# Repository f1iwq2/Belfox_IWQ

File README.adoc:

Carte BELFOX IWQ
================
Carte de remplacement pour portail coulissants BELFOX
pour pilotage de moteurs à courant continu - A base d'arduino nano

Documents dans le fichier pdf
Fichiers schéma Kicad
fichiers gerber dans le répertoire trace

Replacement control board for BELFOX sliding gates
Drive a DC moteur

Documents in pdf files
Kicad board schematics files
gerber files in trace directory

https://youtu.be/OYu1DCdmt-g

image::carte.jpg[]

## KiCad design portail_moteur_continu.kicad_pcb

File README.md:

==============
Carte de remplacement pour portail coulissants BELFOX
pour pilotage de moteurs à courant continu - A base d'arduino nano

Documents dans le fichier pdf
Fichiers schéma Kicad
fichiers gerber dans le répertoire trace

Replacement control board for BELFOX sliding gates
Drive a DC moteur

Documents in pdf files
Kicad board schematics files
gerber files in trace directory

https://youtu.be/OYu1DCdmt-g

image::carte.jpg[]

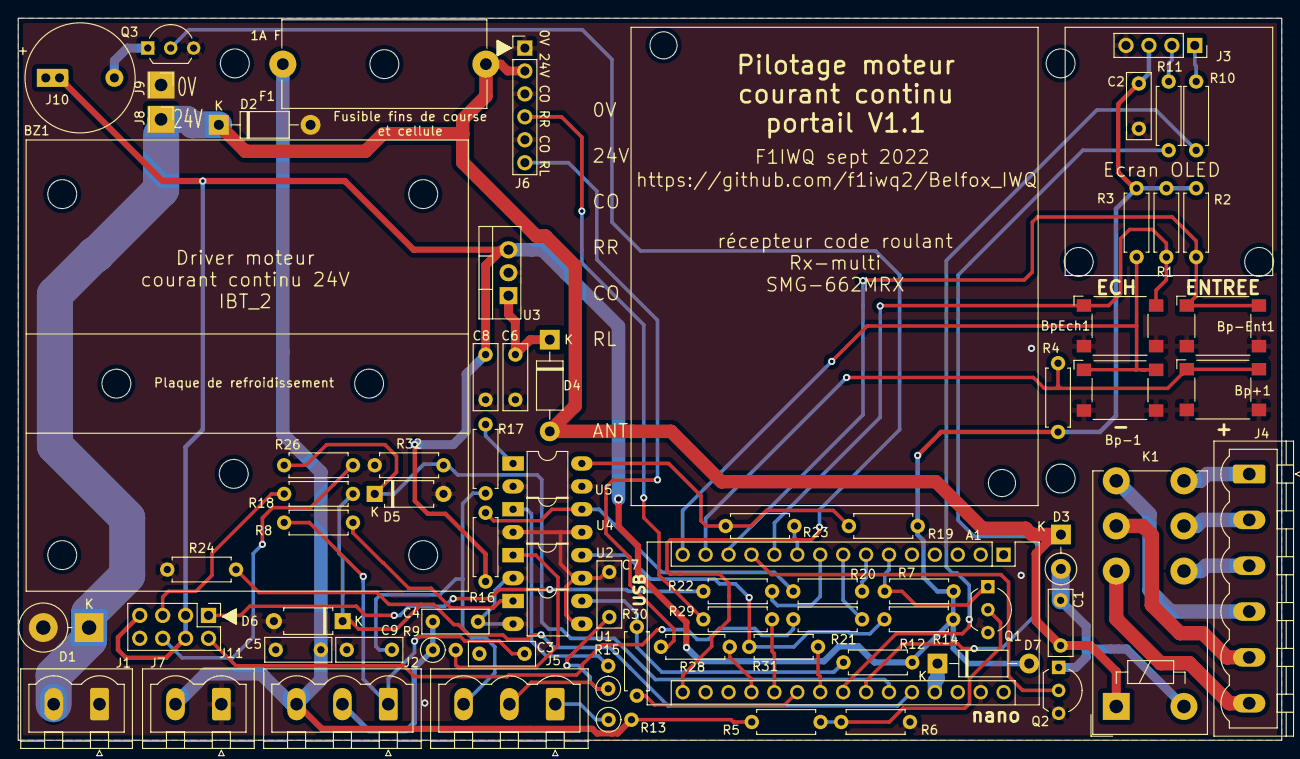
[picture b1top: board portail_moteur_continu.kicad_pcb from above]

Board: 2 copper layers, 140.0 x 80.0 mm, 87 parts (0 on the bottom side), 55 nets.

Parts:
A1: Arduino_Nano_v3.x; Arduino_Nano
BZ1: Buzzer passif; Buzzer_12x9.5RM7.6
Bp+1: SW_MEC_5E; SW_SPST_Omron_B3FS-101xP
Bp-1: SW_MEC_5E; SW_SPST_Omron_B3FS-101xP
Bp-Ent1: SW_MEC_5E; SW_SPST_Omron_B3FS-101xP
BpEch1: SW_MEC_5E; SW_SPST_Omron_B3FS-101xP
C1, C2, C3, C4, C5, C6, C7, C8, C9: 100nF; C_Rect_L7.2mm_W2.5mm_P5.00mm_FKS2_FKP2_MKS2_MKP2
D1: 1.5KE39C; D_DO-201AD_P5.08mm_Vertical_KathodeUp
D2, D4, D7: 1N4004; D_DO-41_SOD81_P10.16mm_Horizontal
D3: 1N4004; D_DO-41_SOD81_P3.81mm_Vertical_KathodeUp
D5, D6: D_Z5.1V; D_A-405_P7.62mm_Horizontal
F1: 1A F; Fuseholder_Cylinder-5x20mm_Schurter_0031_8201_Horizontal_Op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
FID1, FID2, FID3, FID4, FID5, FID6, FID9, FID10, FID11, FID12, FID13, FID14: Fiducial; MountingHole_3.2mm_M3
FID7, FID8: Fiducial; MountingHole_3mm
J1, J7: Screw_Terminal_01x02; PhoenixContact_MSTBVA_2,5_2-G-5,08_1x02_P5.08mm_Vertical
J2, J5: Screw_Terminal_01x03; PhoenixContact_MSTBVA_2,5_3-G-5,08_1x03_P5.08mm_Vertical
J3: Conn_01x04; PinSocket_1x04_P2.54mm_Vertical
J4: Screw_Terminal_01x06; PhoenixContact_MSTBVA_2,5_6-G-5,08_1x06_P5.08mm_Vertical
J6: Conn_01x06_Male; PinHeader_1x06_P2.54mm_Vertical
J8, J9: Conn_01x01_Male; PinHeader_1x01_P2.54mm_Vertical
J10: Conn_01x01_Male; SolderWire-0.25sqmm_1x01_D0.65mm_OD2mm
J11: Conn_01x08_Male; PinHeader_2x04_P2.54mm_Vertical
K1: FINDER-44.62; Relay_DPDT_Finder_40.52
Q1: BC548; TO-92_Inline_Wide
Q2, Q3: BS170; TO-92L_Inline_Wide
R1, R2, R3, R4, R12, R14, R16, R19: 5,6k; R_Axial_DIN0207_L6.3mm_D2.5mm_P7.62mm_Horizontal
R5: 100k; R_Axial_DIN0207_L6.3mm_D2.5mm_P7.62mm_Horizontal
R6: 82k; R_Axial_DIN0207_L6.3mm_D2.5mm_P7.62mm_Horizontal
R7: 10K; R_Axial_DIN0207_L6.3mm_D2.5mm_P7.62mm_Horizontal
R8, R17: 2,7k; R_Axial_DIN0207_L6.3mm_D2.5mm_P7.62mm_Horizontal
R9, R13, R15: 2,7k; R_Axial_DIN0207_L6.3mm_D2.5mm_P2.54mm_Vertical
R10, R11: 330; R_Axial_DIN0207_L6.3mm_D2.5mm_P7.62mm_Horizontal
R18, R26: 5k; R_Axial_DIN0207_L6.3mm_D2.5mm_P7.62mm_Horizontal
R20, R21, R22, R23, R24, R28, R29, R30, R31, R32: 1k; R_Axial_DIN0207_L6.3mm_D2.5mm_P7.62mm_Horizontal
U1, U2, U4, U5: SFH617A-1; DIP-4_W7.62mm_LongPads
U3: LM7805_TO220; TO-220-3_Vertical

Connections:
+5V: BZ1.1, C2.2, C8.1, D7.2, J3.3, J10.1, J11.3, J11.4, J11.7, R1.2, R2.2, R3.2, R4.2, R7.2, R12.1, R14.1, R16.1, R19.1, U3.3
/24V=: C1.1, D1.1, D2.1, D3.1, D4.2, F1.1, J1.2, J6.2, J8.1, K1.A1
/Bp+: A1.14, Bp+1.1, Bp+1.2, R4.1
/Bp-: A1.15, Bp-1.1, Bp-1.2, R3.1
/BpEch: A1.11, BpEch1.1, BpEch1.2, R1.1
/BpEnt: A1.13, Bp-Ent1.1, Bp-Ent1.2, R2.1
/Buz: A1.16, Q3.2
/Cell: C7.1, J5.2, R15.1
/Cellule: R16.2, R20.2, U4.4
/ComCap: C5.1, F1.2, J2.3, J7.2, R5.2, R13.2
/Comand: R19.2, R23.2, U5.4
/Commande: C9.1, J5.3, R17.1
/FOuv: C3.1, J2.1, R8.1
/Ferme: R14.2, R31.1, U2.4
/Ffer: C4.1, J2.2, R9.1
/LIS: J11.6, R26.2
/LPWM: J11.2, R21.2
/Marche: A1.12, Q2.2
/Ouvert: R12.2, R30.1, U1.4
/PFus: A1.6, Q1.1, R7.1
/PLIS: A1.25, D5.1, R26.1, R32.2
/PRIS: A1.26, D6.1, R18.1, R24.2
/RIS: J11.5, R18.2
/RPWM: J11.1, R22.2
/RadioL: J6.6, R28.1
/RadioR: J6.4, R29.1
/SCL: A1.24, R11.2
/SDA: A1.23, R10.2
GND: A1.29, Bp+1.3, Bp+1.4, Bp-1.3, Bp-1.4, Bp-Ent1.3, Bp-Ent1.4, BpEch1.3, BpEch1.4, C2.1, C3.2, C4.2, C5.2, C6.2, C7.2, C8.2, C9.2, D1.2, D2.2, D5.2, D6.2, J1.1, J3.4, J6.1, J6.3, J6.5, J7.1, J9.1, J11.8, Q1.3, Q2.3, Q3.3, R6.1, R24.1, R32.1, U1.2, U1.3, U2.2, U2.3, U3.2, U4.2, U4.3, U5.2, U5.3
unnamed: A1.7, R20.1
unnamed: A1.8, R21.1
unnamed: A1.9, R22.1
unnamed: A1.10, R23.1
unnamed: A1.19, R28.2
unnamed: A1.20, R29.2
unnamed: A1.21, R30.2
unnamed: A1.22, R31.2
unnamed: A1.27, D7.1
unnamed: BZ1.2, Q3.1
unnamed: C1.2, D3.2, K1.A2, Q2.1
unnamed: C6.1, D4.1, U3.1
unnamed: J3.1, R10.1
unnamed: J3.2, R11.1
unnamed: J4.1, K1.24
unnamed: J4.2, K1.21
unnamed: J4.3, K1.22
unnamed: J4.4, K1.14
unnamed: J4.5, K1.11
unnamed: J4.6, K1.12
unnamed: J5.1, R13.1
unnamed: Q1.2, R5.1, R6.2
unnamed: R8.2, U1.1
unnamed: R9.2, U2.1
unnamed: R15.2, U4.1
unnamed: R17.2, U5.1

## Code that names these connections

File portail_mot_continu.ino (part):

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#define   BpP        11     // D11 portB.3 Bouton +
#define   BpE        10     // D10 portB.2 Bouton ENTREE
#define   infomarche  9     // D9  portB.1 Relais K1
#define   BpEch       8     // D8  portB.0 Bouton Ech
#define   Commande    7     // D7  portD.7 Commande ouverture/fermeture 
#define   RPWM        6     // D6  portD.6 pilotage PWM R
#define   LPWM        5     // D5  portD.5 pilotage PWM L
#define   Cellule     4     // D4  portD.4 Photo-cellule
#define   Fuse        3     // D3  portD.3 Fusible F1
#define   rien        2     // D2  portD.2 

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#define   Scl        A5     // portC.5 SCL
#define   Sda        A4     // portC.4 SDA
#define   FcFerme    A3     // portC.3 bit 3 Fin de course fermé
#define   FcOuvert   A2     // portC.2 bit 2 Fin de course ouvert
#define   radiorelR  A1     // portC.1 bit 1 Radio2 par relais
#define   radiorelL  A0     // portC.0 bit 0 Radio1 par relais

// sélection de A6 et A7 du convertisseur analogique - 10 bits valeurs de 0 à 1023.
#define   LIS         6     // A6 image courant L
#define   RIS         7     // A7 image courant H

// vitesses lente et rapide (maxi 255)
#define   lent      150
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  Serial.begin(115200);     // USB
  
  // ports d'entrées et de sorties
  pinMode(RPWM,OUTPUT);
  pinMode(LPWM,OUTPUT);
  pinMode(infomarche,OUTPUT);
  pinMode(BpP,INPUT);
  pinMode(BpM,INPUT);
  pinMode(BpE,INPUT);
  pinMode(BpEch,INPUT);
  pinMode(Fuse,INPUT);
  pinMode(Commande,INPUT);
  pinMode(FcFerme,INPUT);
  pinMode(FcOuvert,INPUT);
  pinMode(Cellule,INPUT);
  pinMode(radiorelL,INPUT_PULLUP);
  pinMode(radiorelR,INPUT_PULLUP);
  pinMode(buzzer,OUTPUT);
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
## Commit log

2022-08-04 initial
2022-09-04 V1.1
2022-09-10 maj 10-09-22
